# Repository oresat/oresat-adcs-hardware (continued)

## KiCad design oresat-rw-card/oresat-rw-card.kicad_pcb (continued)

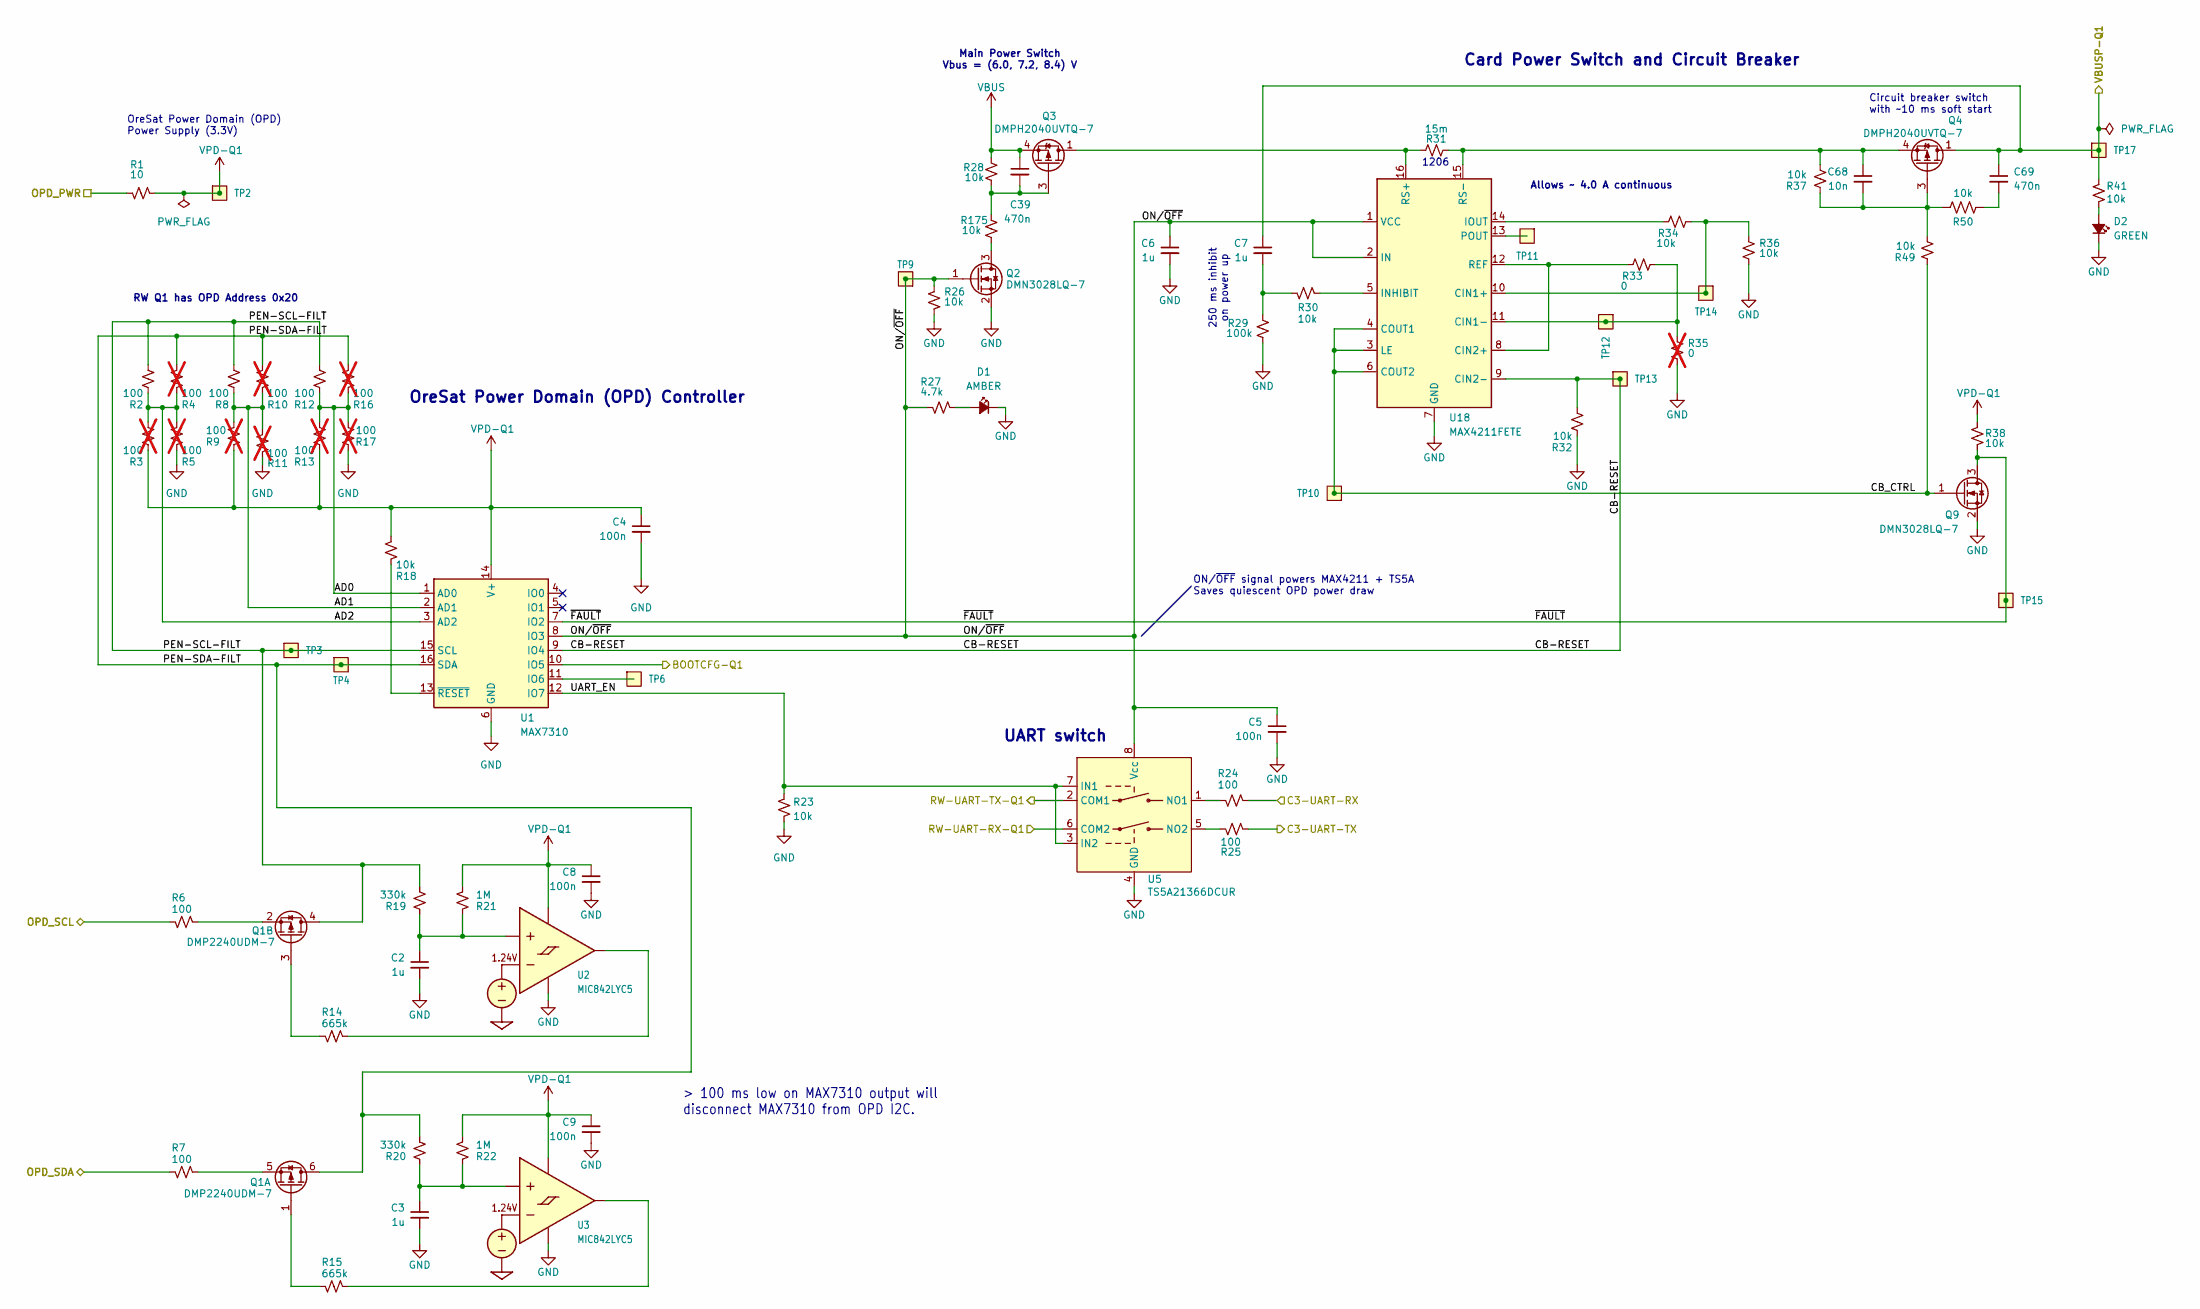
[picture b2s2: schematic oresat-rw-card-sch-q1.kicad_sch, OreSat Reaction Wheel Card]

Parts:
C2, C3, C6, C7: 1u; 0603-C-NOSILK; MPN GRT188R71E105KE13D
C4, C5, C8, C9: 100n; 0603-C-NOSILK; MPN C0603C104K5RACAUTO
C39: 470n; 0603-C-NOSILK; MPN GRT188R71E105KE13D
C68: 10n; 0603-C-NOSILK; MPN C0603C103J5RACAUTO
C69: 470n; 0603-C-NOSILK; MPN C0603C474K3RACAUTO
D1: AMBER; LED_0603_1608Metric_Pad1.05x0.95mm_HandSolder; MPN 150060AS75000
D2: GREEN; LED_0603_1608Metric_Pad1.05x0.95mm_HandSolder; MPN 150060GS75000
Q1: DMP2240UDM-7; SOT-23-6; MPN DMP2240UDM-7
Q2, Q9: DMN3028LQ-7; SOT-23; MPN DMN3028LQ-7
Q3, Q4: DMPH2040UVTQ-7; TSOT-23-6; MPN DMPH2040UVTQ-7
R1: 10; 0603-C-NOSILK; MPN RMCF0603FT10R0
R2, R6, R7, R8, R12, R24, R25: 100; 0603-C-NOSILK; MPN RMCF0603FT100R
R3, R4, R5, R9, R10, R11, R13, R16, R17: 100; 0603-C-NOSILK; not fitted
R14, R15: 665k; 0603-C-NOSILK; MPN RMCF0603FT665K
R18, R23, R26, R28, R30, R32, R34, R36, R37, R38, R41, R49, R50, R175: 10k; 0603-C-NOSILK; MPN RMCF0603FT10K0
R19, R20: 330k; 0603-C-NOSILK; MPN RMCF0603FT330K
R21, R22: 1M; 0603-C-NOSILK; MPN RMCF0603FT1M00
R27: 4.7k; 0603-C-NOSILK; MPN RMCF0603FT4K70
R29: 100k; 0603-C-NOSILK; MPN RMCF0603FT100K
R31: 15m; 1206-C; MPN CSNL1206FT15L0
R33: 0; 0603-C-NOSILK; MPN RMCF0603ZT0R00
R35: 0; 0603-C-NOSILK; not fitted
TP2, TP3, TP4, TP6, TP9, TP10, TP11, TP12, TP13, TP14, TP15, TP17: Test-Point; TestPoint-0.75mm-th
U1: MAX7310; QFN-16-1EP_4x4mm_P0.65mm_EP2.1x2.1mm; MPN MAX7310ATE
U2, U3: MIC842LYC5; SOT-353_SC-70-5; MPN MIC842LYC5-TR
U5: TS5A21366DCUR; VSSOP-8_2.3x2mm_P0.5mm; MPN TS5A21366DCUR
U18: MAX4211FETE; QFN-16-1EP_4x4mm_P0.65mm_EP2.1x2.1mm; MPN MAX4211FETE

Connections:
/C3-UART-RX: R24.1; also elsewhere on the board
/C3-UART-TX: R25.1; also elsewhere on the board
/OPD_PWR: R1.2; also elsewhere on the board
/OPD_SCL: R6.2; also elsewhere on the board
/OPD_SDA: R7.2; also elsewhere on the board
/RW Power Domain Q1/AD0: R12.1, R13.2, R16.1, R17.2, U1.1 (AD0)
/RW Power Domain Q1/AD1: R8.1, R9.2, R10.1, R11.2, U1.2 (AD1)
/RW Power Domain Q1/AD2: R2.1, R3.2, R4.1, R5.2, U1.3 (AD2)
/RW Power Domain Q1/BOOTCFG-Q1: U1.10 (IO5); also elsewhere on the board
/RW Power Domain Q1/CB-RESET: R32.2, TP13.1 (1_1), U1.9 (IO4), U18.9 (CIN2-)
/RW Power Domain Q1/CB_CTRL: Q9.1 (G), R49.1, TP10.1 (1_1), U18.3 (LE), U18.4 (COUT1), U18.6 (COUT2)
/RW Power Domain Q1/ON/~OFF: C5.1, C6.1, Q2.1 (G), R26.1, R27.2, TP9.1 (1_1), U1.8 (IO3), U5.8 (Vcc), U18.1 (VCC), U18.2 (IN)
/RW Power Domain Q1/PEN-SCL-FILT: Q1.4 (D), R2.2, R8.2, R12.2, R19.2, TP3.1 (1_1), U1.15 (SCL)
/RW Power Domain Q1/PEN-SDA-FILT: Q1.6 (D), R4.2, R10.2, R16.2, R20.2, TP4.1 (1_1), U1.16 (SDA)
/RW Power Domain Q1/RW-UART-RX-Q1: U5.6 (COM2); also elsewhere on the board
/RW Power Domain Q1/RW-UART-TX-Q1: U5.2 (COM1); also elsewhere on the board
/RW Power Domain Q1/UART_EN: R23.2, U1.12 (IO7), U5.3 (IN2), U5.7 (IN1)
/RW Power Domain Q1/VBUSP-Q1: C7.1, C69.1, Q4.1 (D), Q4.2 (D), Q4.5 (D), Q4.6 (D), R41.2, TP17.1 (1_1); also elsewhere on the board
/RW Power Domain Q1/~FAULT: Q9.3 (D), R38.1, TP15.1 (1_1), U1.7 (IO2)
GND: C2.2, C3.2, C4.2, C5.2, C6.2, C8.2, C9.2, D1.1 (K), D2.1 (K), Q2.2 (S), Q9.2 (S), R5.1, R11.1, R17.1, R23.1, R26.2, R29.2, R32.1, R35.2, R36.2, U1.6 (GND), U1.17 (GND), U2.2 (GND), U3.2 (GND), U5.4 (GND), U18.7 (GND), U18.17 (GND); also elsewhere on the board
unnamed: C7.2, R29.1, R30.2
unnamed: C69.2, R50.1
unnamed: D1.2 (A), R27.1
unnamed: D2.2 (A), R41.1
unnamed: Q1.1 (G), R15.2
unnamed: Q1.5 (S), R7.1
unnamed: Q1.3 (G), R14.2
unnamed: Q1.2 (S), R6.1
unnamed: Q2.3 (D), R175.2
unnamed: C39.2, Q3.3 (G), R28.2, R175.1
unnamed: C68.2, Q4.3 (G), R37.1, R49.2, R50.2
unnamed: C68.1, Q4.4 (S), R31.2, R37.2, U18.15 (RS-)
unnamed: TP6.1 (1_1), U1.11 (IO6)
unnamed: R18.1, U1.13 (~RESET)
unnamed: C2.1, R19.1, R21.1, U2.1 (INP)
unnamed: R14.1, U2.4 (OUT)
unnamed: C3.1, R20.1, R22.1, U3.1 (INP)
unnamed: R15.1, U3.4 (OUT)
unnamed: R24.2, U5.1 (NO1)
unnamed: R25.2, U5.5 (NO2)
unnamed: R34.1, R36.1, TP14.1 (1_1), U18.10 (CIN1+)
unnamed: R33.1, R35.1, TP12.1 (1_1), U18.11 (CIN1-)
unnamed: R33.2, U18.8 (CIN2+), U18.12 (REF)
unnamed: R30.1, U18.5 (INHIBIT)
unnamed: R34.2, U18.14 (IOUT)
unnamed: TP11.1 (1_1), U18.13 (POUT)
unnamed: Q3.1 (D), Q3.2 (D), Q3.5 (D), Q3.6 (D), R31.1, U18.16 (RS+)
VBUS: C39.1, Q3.4 (S), R28.1; also elsewhere on the board
VPD-Q1: C4.1, C8.1, C9.1, R1.1, R3.1, R9.1, R13.1, R18.2, R21.2, R22.2, R38.2, TP2.1 (1_1), U1.14 (V+), U2.5 (VDD), U3.5 (VDD)

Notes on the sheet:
OreSat Power Domain (OPD) Controller
RW Q1 has OPD Address 0x20
ON/~{OFF} signal powers MAX4211 + TS5A Saves quiescent OPD power draw
Circuit breaker switch with ~10 ms soft start
OreSat Power Domain (OPD) Power Supply (3.3V)
> 100 ms low on MAX7310 output will disconnect MAX7310 from OPD I2C.
250 ms inhibit on power up
1206
Card Power Switch and Circuit Breaker
UART switch
Main Power Switch Vbus = (6.0, 7.2, 8.4) V
Allows ~ 4.0 A continuous

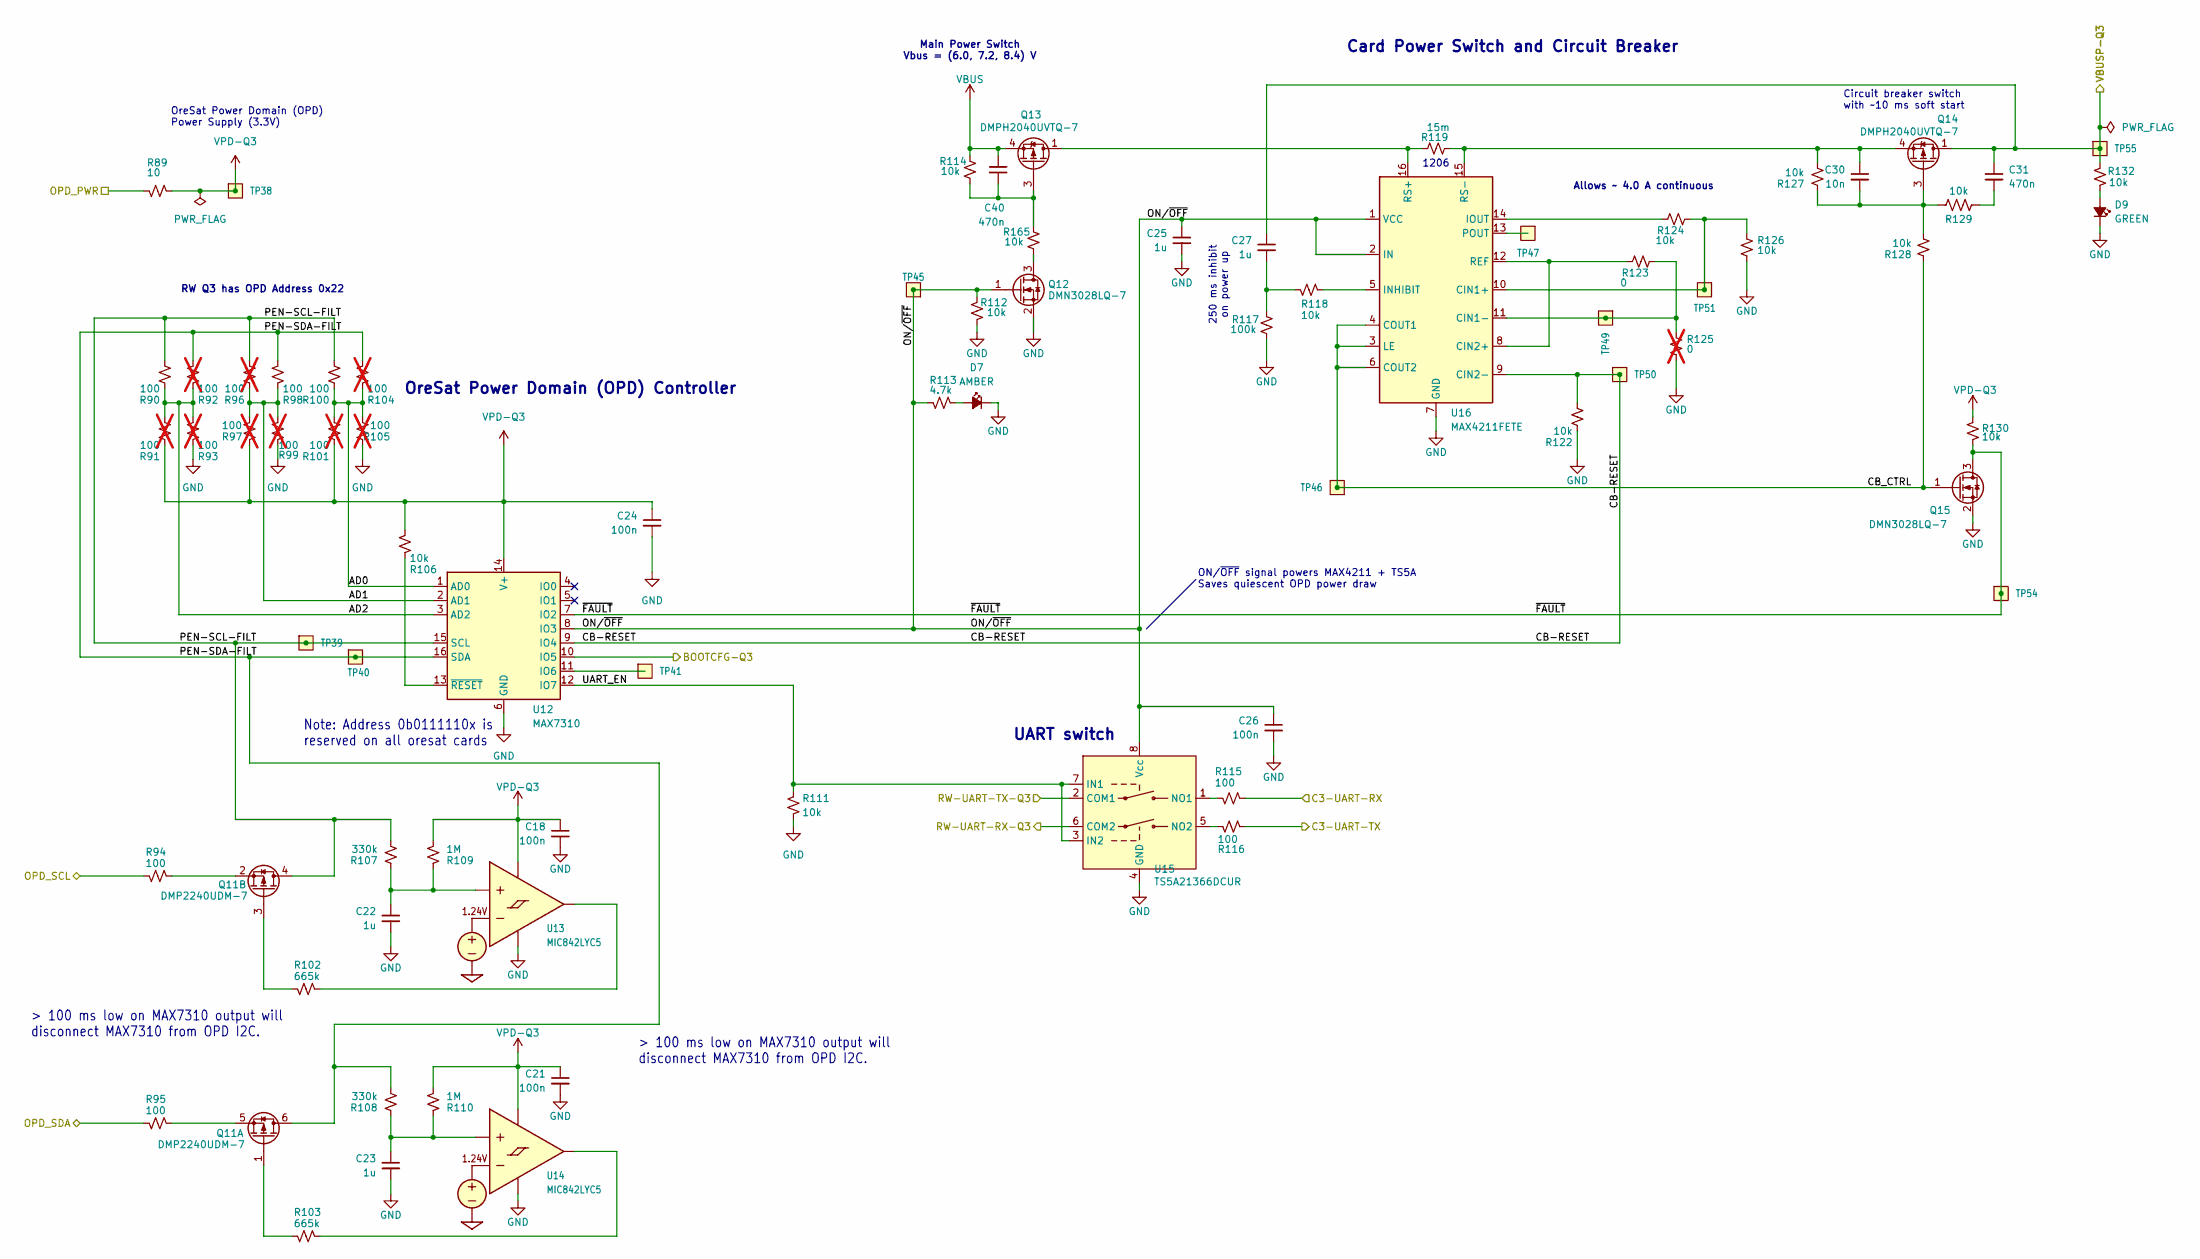
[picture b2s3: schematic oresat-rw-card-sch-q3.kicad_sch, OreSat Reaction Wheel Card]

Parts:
C18, C21, C24, C26: 100n; 0603-C-NOSILK; MPN C0603C104K5RACAUTO
C22, C23, C25, C27: 1u; 0603-C-NOSILK; MPN GRT188R71E105KE13D
C30: 10n; 0603-C-NOSILK; MPN C0603C103J5RACAUTO
C31: 470n; 0603-C-NOSILK; MPN C0603C474K3RACAUTO
C40: 470n; 0603-C-NOSILK; MPN GRT188R71E105KE13D
D7: AMBER; LED_0603_1608Metric_Pad1.05x0.95mm_HandSolder; MPN 150060AS75000
D9: GREEN; LED_0603_1608Metric_Pad1.05x0.95mm_HandSolder; MPN 150060GS75000
Q11: DMP2240UDM-7; SOT-23-6; MPN DMP2240UDM-7
Q12, Q15: DMN3028LQ-7; SOT-23; MPN DMN3028LQ-7
Q13, Q14: DMPH2040UVTQ-7; TSOT-23-6; MPN DMPH2040UVTQ-7
R89: 10; 0603-C-NOSILK; MPN RMCF0603FT10R0
R90, R94, R95, R98, R100, R115, R116: 100; 0603-C-NOSILK; MPN RMCF0603FT100R
R91, R92, R93, R96, R97, R99, R101, R104, R105: 100; 0603-C-NOSILK; not fitted
R102, R103: 665k; 0603-C-NOSILK; MPN RMCF0603FT665K
R106, R111, R112, R114, R118, R122, R124, R126, R127, R128, R129, R130, R132, R165: 10k; 0603-C-NOSILK; MPN RMCF0603FT10K0
R107, R108: 330k; 0603-C-NOSILK; MPN RMCF0603FT330K
R109, R110: 1M; 0603-C-NOSILK; MPN RMCF0603FT1M00
R113: 4.7k; 0603-C-NOSILK; MPN RMCF0603FT4K70
R117: 100k; 0603-C-NOSILK; MPN RMCF0603FT100K
R119: 15m; 1206-C; MPN CSNL1206FT15L0
R123: 0; 0603-C-NOSILK; MPN RMCF0603ZT0R00
R125: 0; 0603-C-NOSILK; not fitted
TP38, TP39, TP40, TP41, TP45, TP46, TP47, TP49, TP50, TP51, TP54, TP55: Test-Point; TestPoint-0.75mm-th
U12: MAX7310; QFN-16-1EP_4x4mm_P0.65mm_EP2.1x2.1mm; MPN MAX7310ATE
U13, U14: MIC842LYC5; SOT-353_SC-70-5; MPN MIC842LYC5-TR
U15: TS5A21366DCUR; VSSOP-8_2.3x2mm_P0.5mm; MPN TS5A21366DCUR
U16: MAX4211FETE; QFN-16-1EP_4x4mm_P0.65mm_EP2.1x2.1mm; MPN MAX4211FETE

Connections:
/C3-UART-RX: R115.1; also elsewhere on the board
/C3-UART-TX: R116.1; also elsewhere on the board
/OPD_PWR: R89.2; also elsewhere on the board
/OPD_SCL: R94.2; also elsewhere on the board
/OPD_SDA: R95.2; also elsewhere on the board
/RW Power Domain Q3/AD0: R100.1, R101.2, R104.1, R105.2, U12.1 (AD0)
/RW Power Domain Q3/AD1: R96.1, R97.2, R98.1, R99.2, U12.2 (AD1)
/RW Power Domain Q3/AD2: R90.1, R91.2, R92.1, R93.2, U12.3 (AD2)
/RW Power Domain Q3/BOOTCFG-Q3: U12.10 (IO5); also elsewhere on the board
/RW Power Domain Q3/CB-RESET: R122.2, TP50.1 (1_1), U12.9 (IO4), U16.9 (CIN2-)
/RW Power Domain Q3/CB_CTRL: Q15.1 (G), R128.1, TP46.1 (1_1), U16.3 (LE), U16.4 (COUT1), U16.6 (COUT2)
/RW Power Domain Q3/ON/~OFF: C25.1, C26.1, Q12.1 (G), R112.1, R113.2, TP45.1 (1_1), U12.8 (IO3), U15.8 (Vcc), U16.1 (VCC), U16.2 (IN)
/RW Power Domain Q3/PEN-SCL-FILT: Q11.4 (D), R90.2, R96.2, R100.2, R107.2, TP39.1 (1_1), U12.15 (SCL)
/RW Power Domain Q3/PEN-SDA-FILT: Q11.6 (D), R92.2, R98.2, R104.2, R108.2, TP40.1 (1_1), U12.16 (SDA)
/RW Power Domain Q3/RW-UART-RX-Q3: U15.6 (COM2); also elsewhere on the board
/RW Power Domain Q3/RW-UART-TX-Q3: U15.2 (COM1); also elsewhere on the board
/RW Power Domain Q3/UART_EN: R111.2, U12.12 (IO7), U15.3 (IN2), U15.7 (IN1)
/RW Power Domain Q3/VBUSP-Q3: C27.1, C31.1, Q14.1 (D), Q14.2 (D), Q14.5 (D), Q14.6 (D), R132.2, TP55.1 (1_1); also elsewhere on the board
/RW Power Domain Q3/~FAULT: Q15.3 (D), R130.1, TP54.1 (1_1), U12.7 (IO2)
GND: C18.2, C21.2, C22.2, C23.2, C24.2, C25.2, C26.2, D7.1 (K), D9.1 (K), Q12.2 (S), Q15.2 (S), R93.1, R99.1, R105.1, R111.1, R112.2, R117.2, R122.1, R125.2, R126.2, U12.6 (GND), U12.17 (GND), U13.2 (GND), U14.2 (GND), U15.4 (GND), U16.7 (GND), U16.17 (GND); also elsewhere on the board
unnamed: C27.2, R117.1, R118.2
unnamed: C31.2, R129.1
unnamed: D7.2 (A), R113.1
unnamed: D9.2 (A), R132.1
unnamed: Q11.1 (G), R103.2
unnamed: Q11.5 (S), R95.1
unnamed: Q11.3 (G), R102.2
unnamed: Q11.2 (S), R94.1
unnamed: Q12.3 (D), R165.2
unnamed: C40.2, Q13.3 (G), R114.2, R165.1
unnamed: C30.2, Q14.3 (G), R127.1, R128.2, R129.2
unnamed: C30.1, Q14.4 (S), R119.2, R127.2, U16.15 (RS-)
unnamed: TP41.1 (1_1), U12.11 (IO6)
unnamed: R106.1, U12.13 (~RESET)
unnamed: C22.1, R107.1, R109.1, U13.1 (INP)
unnamed: R102.1, U13.4 (OUT)
unnamed: C23.1, R108.1, R110.1, U14.1 (INP)
unnamed: R103.1, U14.4 (OUT)
unnamed: R115.2, U15.1 (NO1)
unnamed: R116.2, U15.5 (NO2)
unnamed: R124.1, R126.1, TP51.1 (1_1), U16.10 (CIN1+)
unnamed: R123.1, R125.1, TP49.1 (1_1), U16.11 (CIN1-)
unnamed: R123.2, U16.8 (CIN2+), U16.12 (REF)
unnamed: R118.1, U16.5 (INHIBIT)
unnamed: R124.2, U16.14 (IOUT)
unnamed: TP47.1 (1_1), U16.13 (POUT)
unnamed: Q13.1 (D), Q13.2 (D), Q13.5 (D), Q13.6 (D), R119.1, U16.16 (RS+)
VBUS: C40.1, Q13.4 (S), R114.1; also elsewhere on the board
VPD-Q3: C18.1, C21.1, C24.1, R89.1, R91.1, R97.1, R101.1, R106.2, R109.2, R110.2, R130.2, TP38.1 (1_1), U12.14 (V+), U13.5 (VDD), U14.5 (VDD)

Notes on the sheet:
Card Power Switch and Circuit Breaker
250 ms inhibit on power up
OreSat Power Domain (OPD) Controller
RW Q3 has OPD Address 0x22
ON/~{OFF} signal powers MAX4211 + TS5A Saves quiescent OPD power draw
Circuit breaker switch with ~10 ms soft start
OreSat Power Domain (OPD) Power Supply (3.3V)
UART switch
> 100 ms low on MAX7310 output will disconnect MAX7310 from OPD I2C.
Main Power Switch Vbus = (6.0, 7.2, 8.4) V
Note: Address 0b0111110x is reserved on all oresat cards
1206
Allows ~ 4.0 A continuous

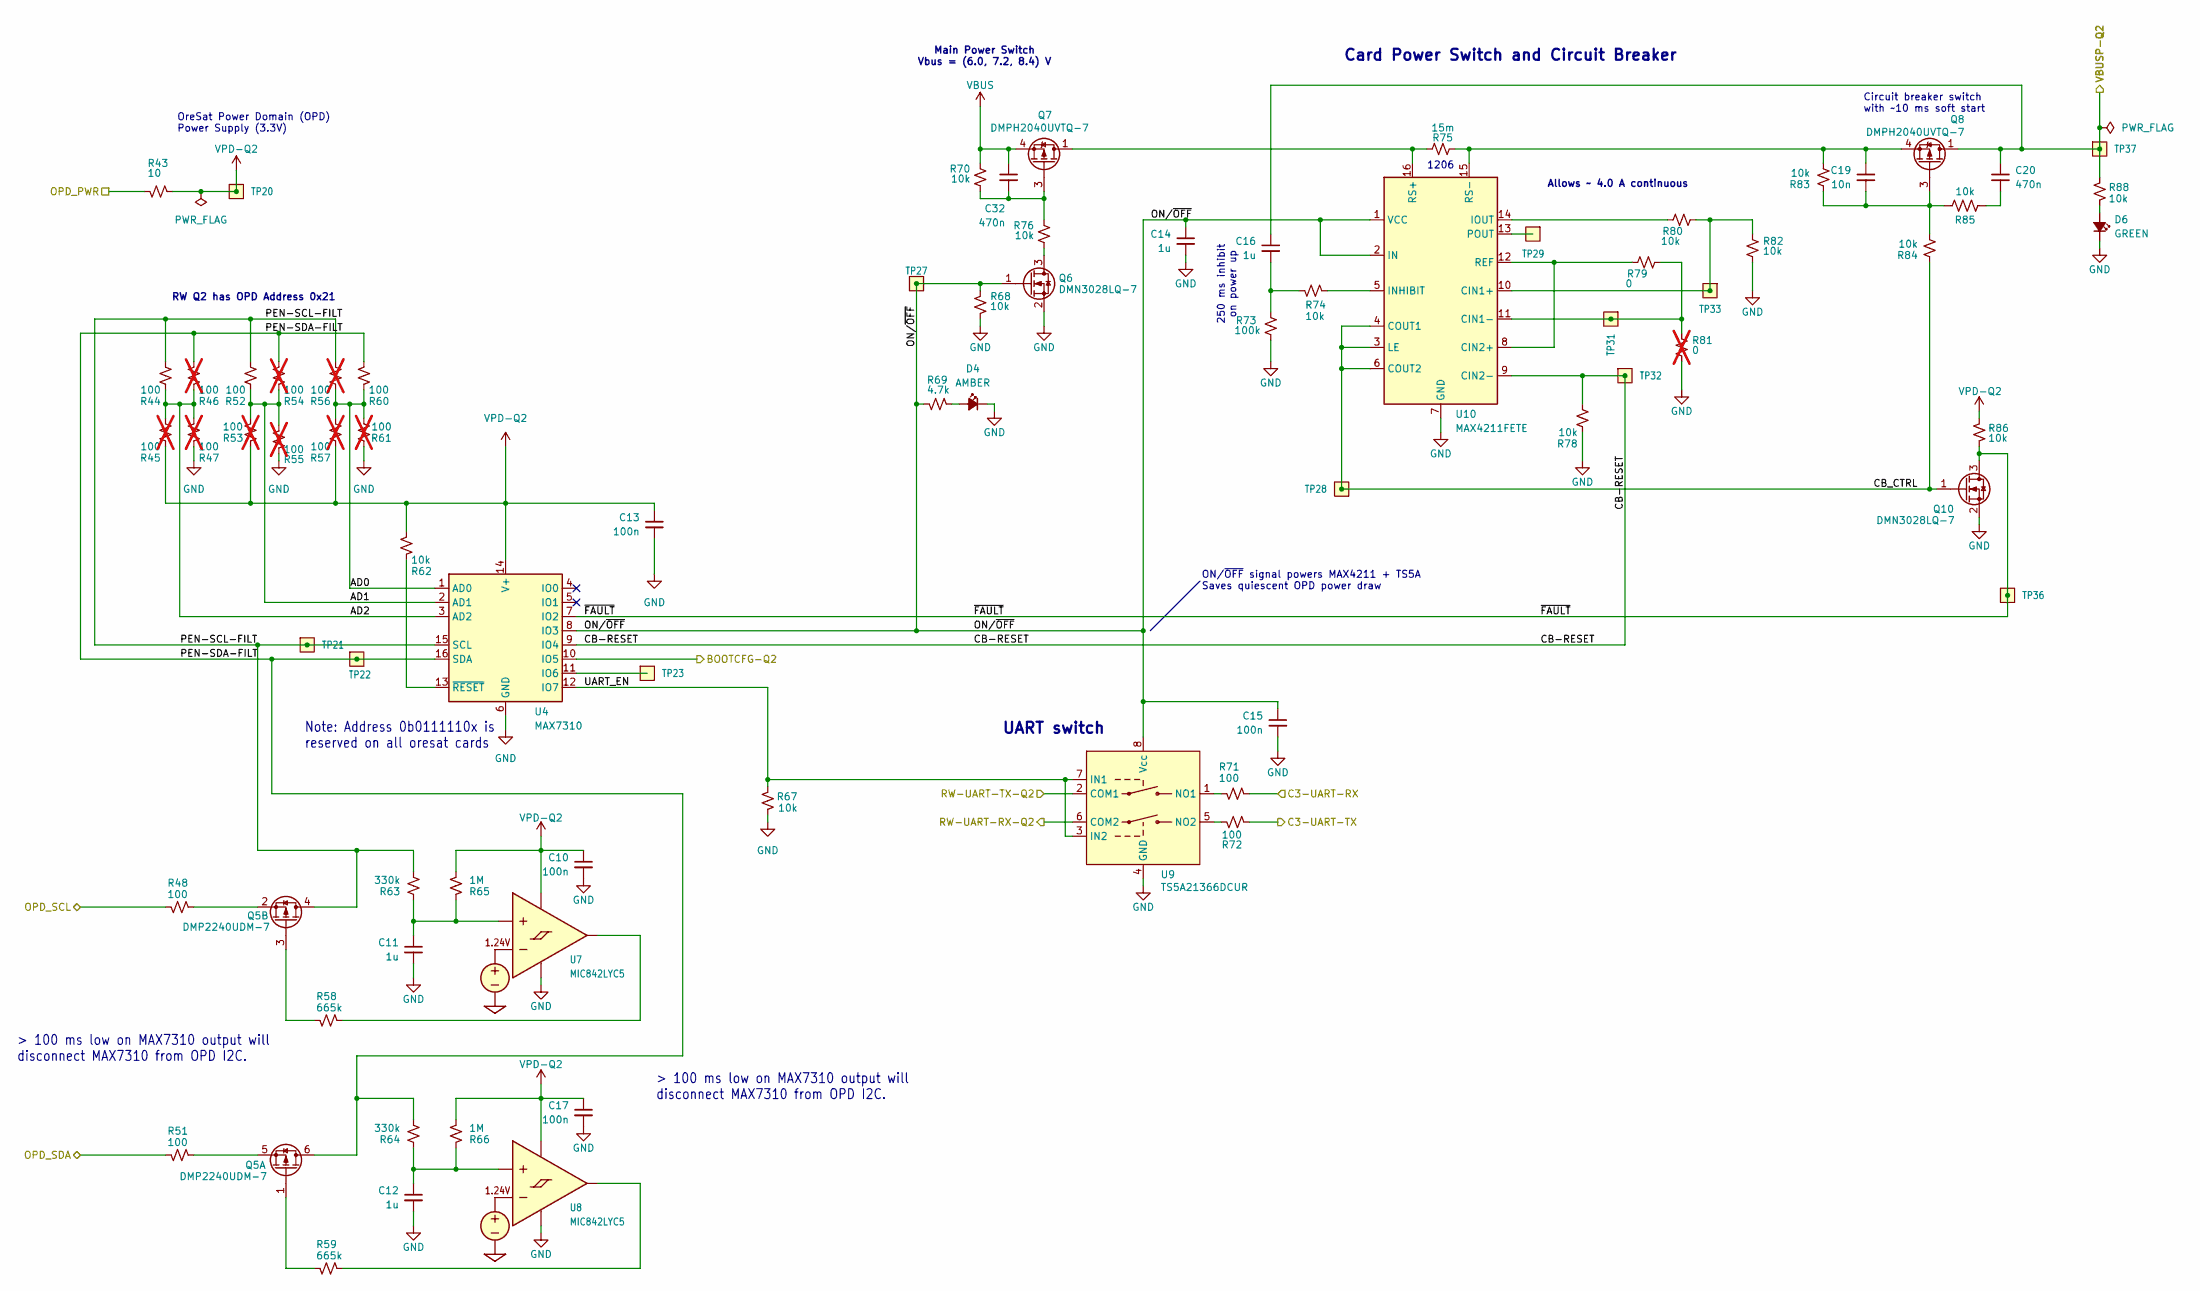
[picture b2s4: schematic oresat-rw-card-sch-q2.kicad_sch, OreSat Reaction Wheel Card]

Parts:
C10, C13, C15, C17: 100n; 0603-C-NOSILK; MPN C0603C104K5RACAUTO
C11, C12, C14, C16: 1u; 0603-C-NOSILK; MPN GRT188R71E105KE13D
C19: 10n; 0603-C-NOSILK; MPN C0603C103J5RACAUTO
C20: 470n; 0603-C-NOSILK; MPN C0603C474K3RACAUTO
C32: 470n; 0603-C-NOSILK; MPN GRT188R71E105KE13D
D4: AMBER; LED_0603_1608Metric_Pad1.05x0.95mm_HandSolder; MPN 150060AS75000
D6: GREEN; LED_0603_1608Metric_Pad1.05x0.95mm_HandSolder; MPN 150060GS75000
Q5: DMP2240UDM-7; SOT-23-6; MPN DMP2240UDM-7
Q6, Q10: DMN3028LQ-7; SOT-23; MPN DMN3028LQ-7
Q7, Q8: DMPH2040UVTQ-7; TSOT-23-6; MPN DMPH2040UVTQ-7
R43: 10; 0603-C-NOSILK; MPN RMCF0603FT10R0
R44, R48, R51, R52, R60, R71, R72: 100; 0603-C-NOSILK; MPN RMCF0603FT100R
R45, R46, R47, R53, R54, R55, R56, R57, R61: 100; 0603-C-NOSILK; not fitted
R58, R59: 665k; 0603-C-NOSILK; MPN RMCF0603FT665K
R62, R67, R68, R70, R74, R76, R78, R80, R82, R83, R84, R85, R86, R88: 10k; 0603-C-NOSILK; MPN RMCF0603FT10K0
R63, R64: 330k; 0603-C-NOSILK; MPN RMCF0603FT330K
R65, R66: 1M; 0603-C-NOSILK; MPN RMCF0603FT1M00
R69: 4.7k; 0603-C-NOSILK; MPN RMCF0603FT4K70
R73: 100k; 0603-C-NOSILK; MPN RMCF0603FT100K
R75: 15m; 1206-C; MPN CSNL1206FT15L0
R79: 0; 0603-C-NOSILK; MPN RMCF0603ZT0R00
R81: 0; 0603-C-NOSILK; not fitted
TP20, TP21, TP22, TP23, TP27, TP28, TP29, TP31, TP32, TP33, TP36, TP37: Test-Point; TestPoint-0.75mm-th
U4: MAX7310; QFN-16-1EP_4x4mm_P0.65mm_EP2.1x2.1mm; MPN MAX7310ATE
U7, U8: MIC842LYC5; SOT-353_SC-70-5; MPN MIC842LYC5-TR
U9: TS5A21366DCUR; VSSOP-8_2.3x2mm_P0.5mm; MPN TS5A21366DCUR
U10: MAX4211FETE; QFN-16-1EP_4x4mm_P0.65mm_EP2.1x2.1mm; MPN MAX4211FETE

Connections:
/C3-UART-RX: R71.1; also elsewhere on the board
/C3-UART-TX: R72.1; also elsewhere on the board
/OPD_PWR: R43.2; also elsewhere on the board
/OPD_SCL: R48.2; also elsewhere on the board
/OPD_SDA: R51.2; also elsewhere on the board
/RW Power Domain Q2/AD0: R56.1, R57.2, R60.1, R61.2, U4.1 (AD0)
/RW Power Domain Q2/AD1: R52.1, R53.2, R54.1, R55.2, U4.2 (AD1)
/RW Power Domain Q2/AD2: R44.1, R45.2, R46.1, R47.2, U4.3 (AD2)
/RW Power Domain Q2/BOOTCFG-Q2: U4.10 (IO5); also elsewhere on the board
/RW Power Domain Q2/CB-RESET: R78.2, TP32.1 (1_1), U4.9 (IO4), U10.9 (CIN2-)
/RW Power Domain Q2/CB_CTRL: Q10.1 (G), R84.1, TP28.1 (1_1), U10.3 (LE), U10.4 (COUT1), U10.6 (COUT2)
/RW Power Domain Q2/ON/~OFF: C14.1, C15.1, Q6.1 (G), R68.1, R69.2, TP27.1 (1_1), U4.8 (IO3), U9.8 (Vcc), U10.1 (VCC), U10.2 (IN)
/RW Power Domain Q2/PEN-SCL-FILT: Q5.4 (D), R44.2, R52.2, R56.2, R63.2, TP21.1 (1_1), U4.15 (SCL)
/RW Power Domain Q2/PEN-SDA-FILT: Q5.6 (D), R46.2, R54.2, R60.2, R64.2, TP22.1 (1_1), U4.16 (SDA)
/RW Power Domain Q2/RW-UART-RX-Q2: U9.6 (COM2); also elsewhere on the board
/RW Power Domain Q2/RW-UART-TX-Q2: U9.2 (COM1); also elsewhere on the board
/RW Power Domain Q2/UART_EN: R67.2, U4.12 (IO7), U9.3 (IN2), U9.7 (IN1)
/RW Power Domain Q2/VBUSP-Q2: C16.1, C20.1, Q8.1 (D), Q8.2 (D), Q8.5 (D), Q8.6 (D), R88.2, TP37.1 (1_1); also elsewhere on the board
/RW Power Domain Q2/~FAULT: Q10.3 (D), R86.1, TP36.1 (1_1), U4.7 (IO2)
GND: C10.2, C11.2, C12.2, C13.2, C14.2, C15.2, C17.2, D4.1 (K), D6.1 (K), Q6.2 (S), Q10.2 (S), R47.1, R55.1, R61.1, R67.1, R68.2, R73.2, R78.1, R81.2, R82.2, U4.6 (GND), U4.17 (GND), U7.2 (GND), U8.2 (GND), U9.4 (GND), U10.7 (GND), U10.17 (GND); also elsewhere on the board
unnamed: C16.2, R73.1, R74.2
unnamed: C20.2, R85.1
unnamed: D4.2 (A), R69.1
unnamed: D6.2 (A), R88.1
unnamed: Q5.1 (G), R59.2
unnamed: Q5.5 (S), R51.1
unnamed: Q5.3 (G), R58.2
unnamed: Q5.2 (S), R48.1
unnamed: Q6.3 (D), R76.2
unnamed: C32.2, Q7.3 (G), R70.2, R76.1
unnamed: C19.2, Q8.3 (G), R83.1, R84.2, R85.2
unnamed: C19.1, Q8.4 (S), R75.2, R83.2, U10.15 (RS-)
unnamed: TP23.1 (1_1), U4.11 (IO6)
unnamed: R62.1, U4.13 (~RESET)
unnamed: C11.1, R63.1, R65.1, U7.1 (INP)
unnamed: R58.1, U7.4 (OUT)
unnamed: C12.1, R64.1, R66.1, U8.1 (INP)
unnamed: R59.1, U8.4 (OUT)
unnamed: R71.2, U9.1 (NO1)
unnamed: R72.2, U9.5 (NO2)
unnamed: R80.1, R82.1, TP33.1 (1_1), U10.10 (CIN1+)
unnamed: R79.1, R81.1, TP31.1 (1_1), U10.11 (CIN1-)
unnamed: R79.2, U10.8 (CIN2+), U10.12 (REF)
unnamed: R74.1, U10.5 (INHIBIT)
unnamed: R80.2, U10.14 (IOUT)
unnamed: TP29.1 (1_1), U10.13 (POUT)
unnamed: Q7.1 (D), Q7.2 (D), Q7.5 (D), Q7.6 (D), R75.1, U10.16 (RS+)
VBUS: C32.1, Q7.4 (S), R70.1; also elsewhere on the board
VPD-Q2: C10.1, C13.1, C17.1, R43.1, R45.1, R53.1, R57.1, R62.2, R65.2, R66.2, R86.2, TP20.1 (1_1), U4.14 (V+), U7.5 (VDD), U8.5 (VDD)

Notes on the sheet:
Circuit breaker switch with ~10 ms soft start
Main Power Switch Vbus = (6.0, 7.2, 8.4) V
OreSat Power Domain (OPD) Power Supply (3.3V)
Card Power Switch and Circuit Breaker
Allows ~ 4.0 A continuous
ON/~{OFF} signal powers MAX4211 + TS5A Saves quiescent OPD power draw
RW Q2 has OPD Address 0x21
1206
Note: Address 0b0111110x is reserved on all oresat cards
> 100 ms low on MAX7310 output will disconnect MAX7310 from OPD I2C.
UART switch
250 ms inhibit on power up

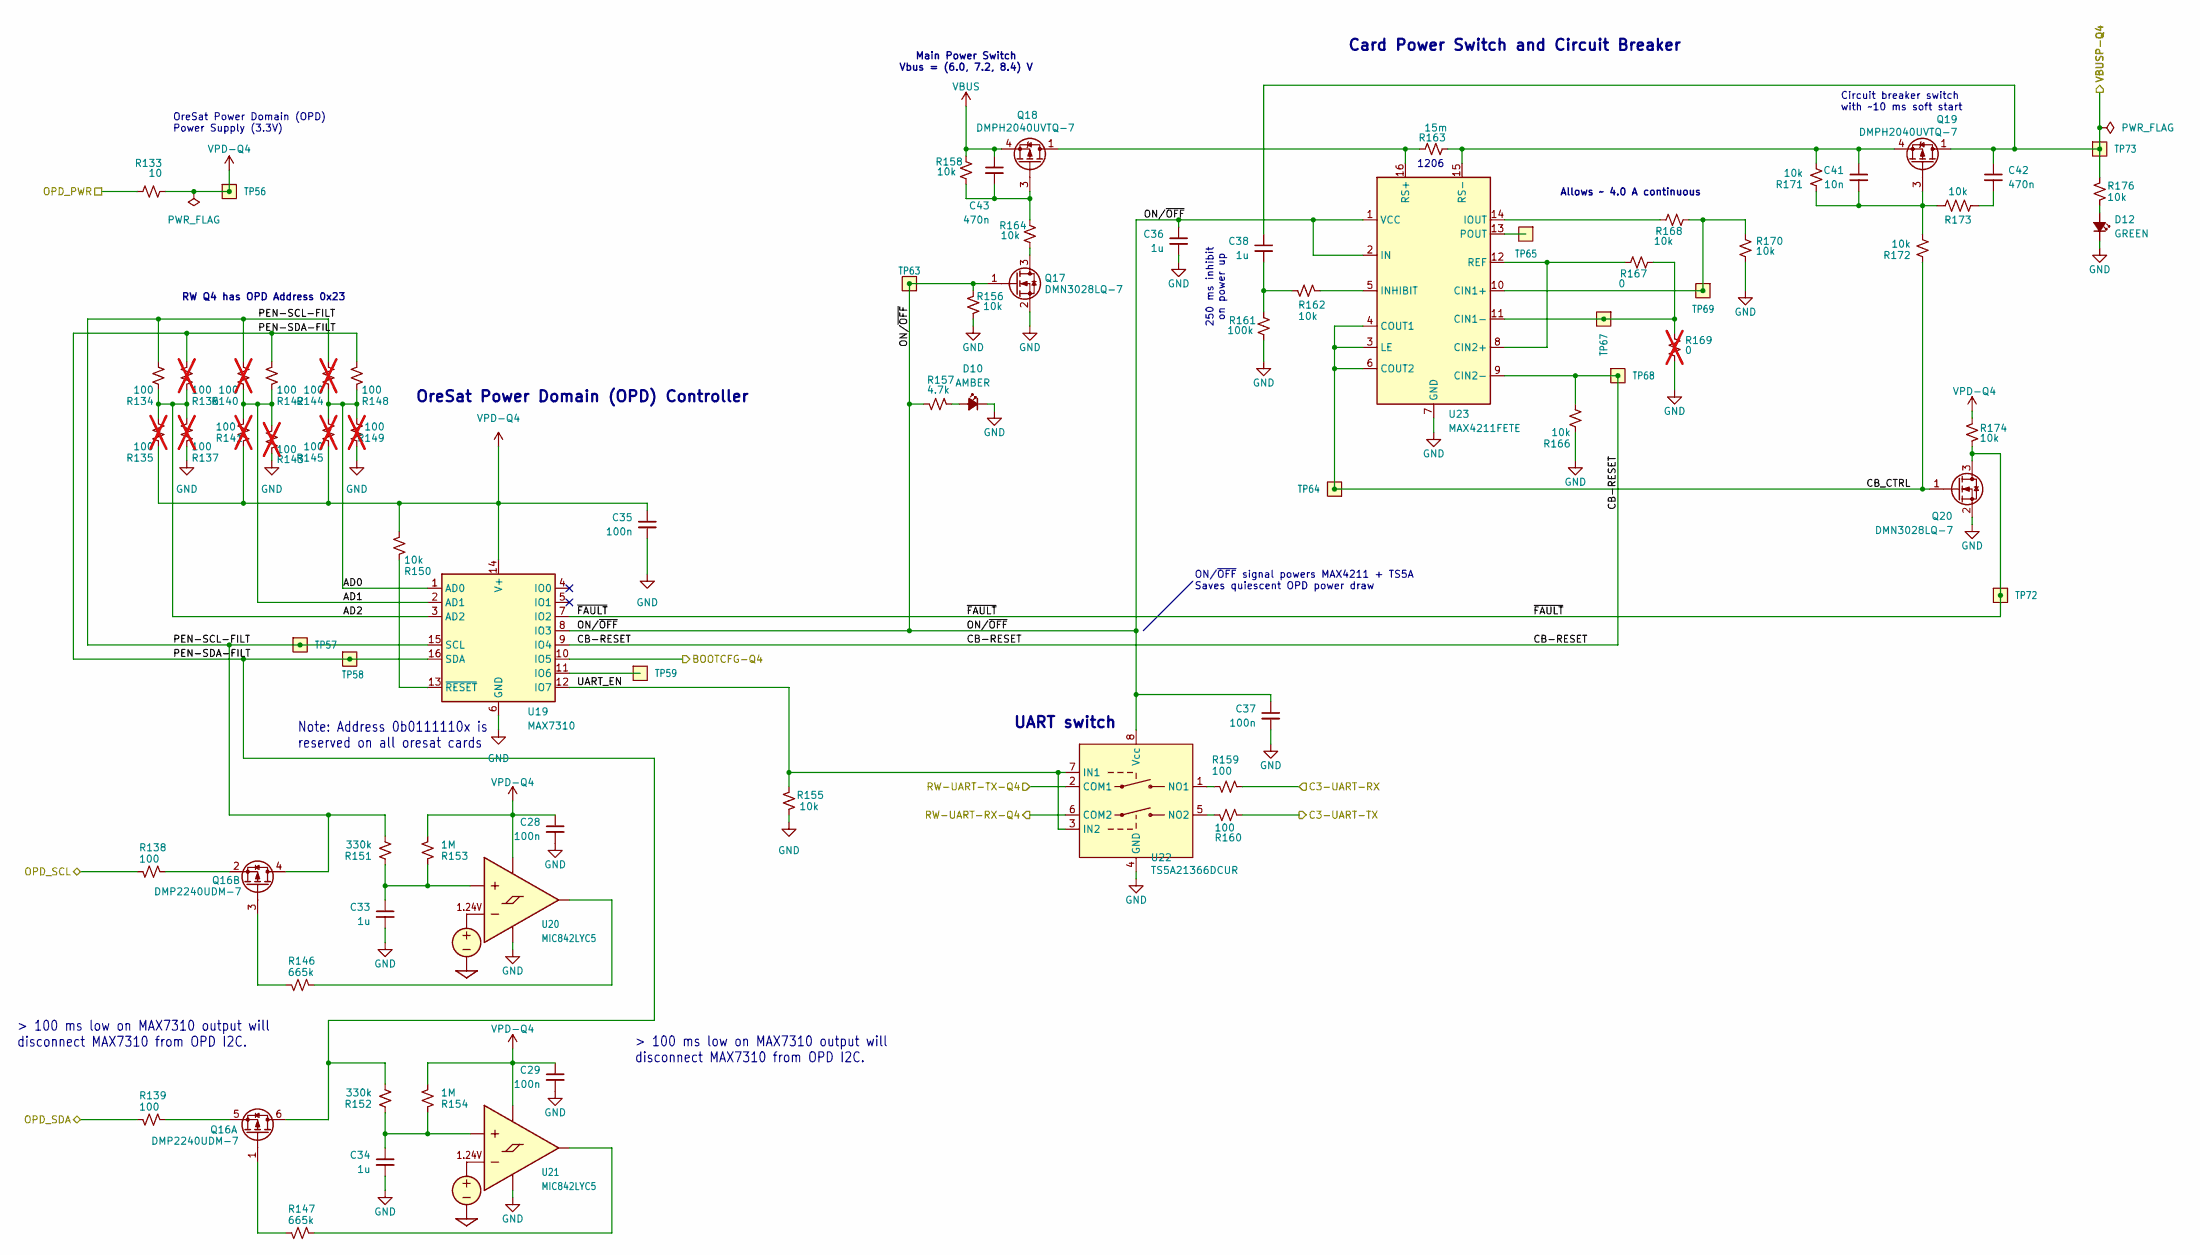
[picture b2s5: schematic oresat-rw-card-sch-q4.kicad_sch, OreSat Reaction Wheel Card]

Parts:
C28, C29, C35, C37: 100n; 0603-C-NOSILK; MPN C0603C104K5RACAUTO
C33, C34, C36, C38: 1u; 0603-C-NOSILK; MPN GRT188R71E105KE13D
C41: 10n; 0603-C-NOSILK; MPN C0603C103J5RACAUTO
C42: 470n; 0603-C-NOSILK; MPN C0603C474K3RACAUTO
C43: 470n; 0603-C-NOSILK; MPN GRT188R71E105KE13D
D10: AMBER; LED_0603_1608Metric_Pad1.05x0.95mm_HandSolder; MPN 150060AS75000
D12: GREEN; LED_0603_1608Metric_Pad1.05x0.95mm_HandSolder; MPN 150060GS75000
Q16: DMP2240UDM-7; SOT-23-6; MPN DMP2240UDM-7
Q17, Q20: DMN3028LQ-7; SOT-23; MPN DMN3028LQ-7
Q18, Q19: DMPH2040UVTQ-7; TSOT-23-6; MPN DMPH2040UVTQ-7
R133: 10; 0603-C-NOSILK; MPN RMCF0603FT10R0
R134, R138, R139, R142, R148, R159, R160: 100; 0603-C-NOSILK; MPN RMCF0603FT100R
R135, R136, R137, R140, R141, R143, R144, R145, R149: 100; 0603-C-NOSILK; not fitted
R146, R147: 665k; 0603-C-NOSILK; MPN RMCF0603FT665K
R150, R155, R156, R158, R162, R164, R166, R168, R170, R171, R172, R173, R174, R176: 10k; 0603-C-NOSILK; MPN RMCF0603FT10K0
R151, R152: 330k; 0603-C-NOSILK; MPN RMCF0603FT330K
R153, R154: 1M; 0603-C-NOSILK; MPN RMCF0603FT1M00
R157: 4.7k; 0603-C-NOSILK; MPN RMCF0603FT4K70
R161: 100k; 0603-C-NOSILK; MPN RMCF0603FT100K
R163: 15m; 1206-C; MPN CSNL1206FT15L0
R167: 0; 0603-C-NOSILK; MPN RMCF0603ZT0R00
R169: 0; 0603-C-NOSILK; not fitted
TP56, TP57, TP58, TP59, TP63, TP64, TP65, TP67, TP68, TP69, TP72, TP73: Test-Point; TestPoint-0.75mm-th
U19: MAX7310; QFN-16-1EP_4x4mm_P0.65mm_EP2.1x2.1mm; MPN MAX7310ATE
U20, U21: MIC842LYC5; SOT-353_SC-70-5; MPN MIC842LYC5-TR
U22: TS5A21366DCUR; VSSOP-8_2.3x2mm_P0.5mm; MPN TS5A21366DCUR
U23: MAX4211FETE; QFN-16-1EP_4x4mm_P0.65mm_EP2.1x2.1mm; MPN MAX4211FETE

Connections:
/C3-UART-RX: R159.1; also elsewhere on the board
/C3-UART-TX: R160.1; also elsewhere on the board
/OPD_PWR: R133.1; also elsewhere on the board
/OPD_SCL: R138.2; also elsewhere on the board
/OPD_SDA: R139.2; also elsewhere on the board
/RW Power Domain Q4/AD0: R144.1, R145.2, R148.1, R149.2, U19.1 (AD0)
/RW Power Domain Q4/AD1: R140.1, R141.2, R142.1, R143.2, U19.2 (AD1)
/RW Power Domain Q4/AD2: R134.1, R135.2, R136.1, R137.2, U19.3 (AD2)
/RW Power Domain Q4/BOOTCFG-Q4: U19.10 (IO5); also elsewhere on the board
/RW Power Domain Q4/CB-RESET: R166.2, TP68.1 (1_1), U19.9 (IO4), U23.9 (CIN2-)
/RW Power Domain Q4/CB_CTRL: Q20.1 (G), R172.1, TP64.1 (1_1), U23.3 (LE), U23.4 (COUT1), U23.6 (COUT2)
/RW Power Domain Q4/ON/~OFF: C36.1, C37.1, Q17.1 (G), R156.1, R157.2, TP63.1 (1_1), U19.8 (IO3), U22.8 (Vcc), U23.1 (VCC), U23.2 (IN)
/RW Power Domain Q4/PEN-SCL-FILT: Q16.4 (D), R134.2, R140.2, R144.2, R151.2, TP57.1 (1_1), U19.15 (SCL)
/RW Power Domain Q4/PEN-SDA-FILT: Q16.6 (D), R136.2, R142.2, R148.2, R152.2, TP58.1 (1_1), U19.16 (SDA)
/RW Power Domain Q4/RW-UART-RX-Q4: U22.6 (COM2); also elsewhere on the board
/RW Power Domain Q4/RW-UART-TX-Q4: U22.2 (COM1); also elsewhere on the board
/RW Power Domain Q4/UART_EN: R155.2, U19.12 (IO7), U22.3 (IN2), U22.7 (IN1)
/RW Power Domain Q4/VBUSP-Q4: C38.1, C42.1, Q19.1 (D), Q19.2 (D), Q19.5 (D), Q19.6 (D), R176.2, TP73.1 (1_1); also elsewhere on the board
/RW Power Domain Q4/~FAULT: Q20.3 (D), R174.1, TP72.1 (1_1), U19.7 (IO2)
GND: C28.2, C29.2, C33.2, C34.2, C35.2, C36.2, C37.2, D10.1 (K), D12.1 (K), Q17.2 (S), Q20.2 (S), R137.1, R143.1, R149.1, R155.1, R156.2, R161.2, R166.1, R169.2, R170.2, U19.6 (GND), U19.17 (GND), U20.2 (GND), U21.2 (GND), U22.4 (GND), U23.7 (GND), U23.17 (GND); also elsewhere on the board
unnamed: C38.2, R161.1, R162.2
unnamed: C42.2, R173.1
unnamed: D10.2 (A), R157.1
unnamed: D12.2 (A), R176.1
unnamed: Q16.1 (G), R147.2
unnamed: Q16.5 (S), R139.1
unnamed: Q16.3 (G), R146.2
unnamed: Q16.2 (S), R138.1
unnamed: Q17.3 (D), R164.2
unnamed: C43.2, Q18.3 (G), R158.2, R164.1
unnamed: C41.2, Q19.3 (G), R171.1, R172.2, R173.2
unnamed: C41.1, Q19.4 (S), R163.2, R171.2, U23.15 (RS-)
unnamed: TP59.1 (1_1), U19.11 (IO6)
unnamed: R150.1, U19.13 (~RESET)
unnamed: C33.1, R151.1, R153.1, U20.1 (INP)
unnamed: R146.1, U20.4 (OUT)
unnamed: C34.1, R152.1, R154.1, U21.1 (INP)
unnamed: R147.1, U21.4 (OUT)
unnamed: R159.2, U22.1 (NO1)
unnamed: R160.2, U22.5 (NO2)
unnamed: R168.1, R170.1, TP69.1 (1_1), U23.10 (CIN1+)
unnamed: R167.1, R169.1, TP67.1 (1_1), U23.11 (CIN1-)
unnamed: R167.2, U23.8 (CIN2+), U23.12 (REF)
unnamed: R162.1, U23.5 (INHIBIT)
unnamed: R168.2, U23.14 (IOUT)
unnamed: TP65.1 (1_1), U23.13 (POUT)
unnamed: Q18.1 (D), Q18.2 (D), Q18.5 (D), Q18.6 (D), R163.1, U23.16 (RS+)
VBUS: C43.1, Q18.4 (S), R158.1; also elsewhere on the board
VPD-Q4: C28.1, C29.1, C35.1, R133.2, R135.1, R141.1, R145.1, R150.2, R153.2, R154.2, R174.2, TP56.1 (1_1), U19.14 (V+), U20.5 (VDD), U21.5 (VDD)

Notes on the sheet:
ON/~{OFF} signal powers MAX4211 + TS5A Saves quiescent OPD power draw
OreSat Power Domain (OPD) Power Supply (3.3V)
Allows ~ 4.0 A continuous
UART switch
> 100 ms low on MAX7310 output will disconnect MAX7310 from OPD I2C.
1206
Main Power Switch Vbus = (6.0, 7.2, 8.4) V
Card Power Switch and Circuit Breaker
Circuit breaker switch with ~10 ms soft start
Note: Address 0b0111110x is reserved on all oresat cards
250 ms inhibit on power up
OreSat Power Domain (OPD) Controller
RW Q4 has OPD Address 0x23
